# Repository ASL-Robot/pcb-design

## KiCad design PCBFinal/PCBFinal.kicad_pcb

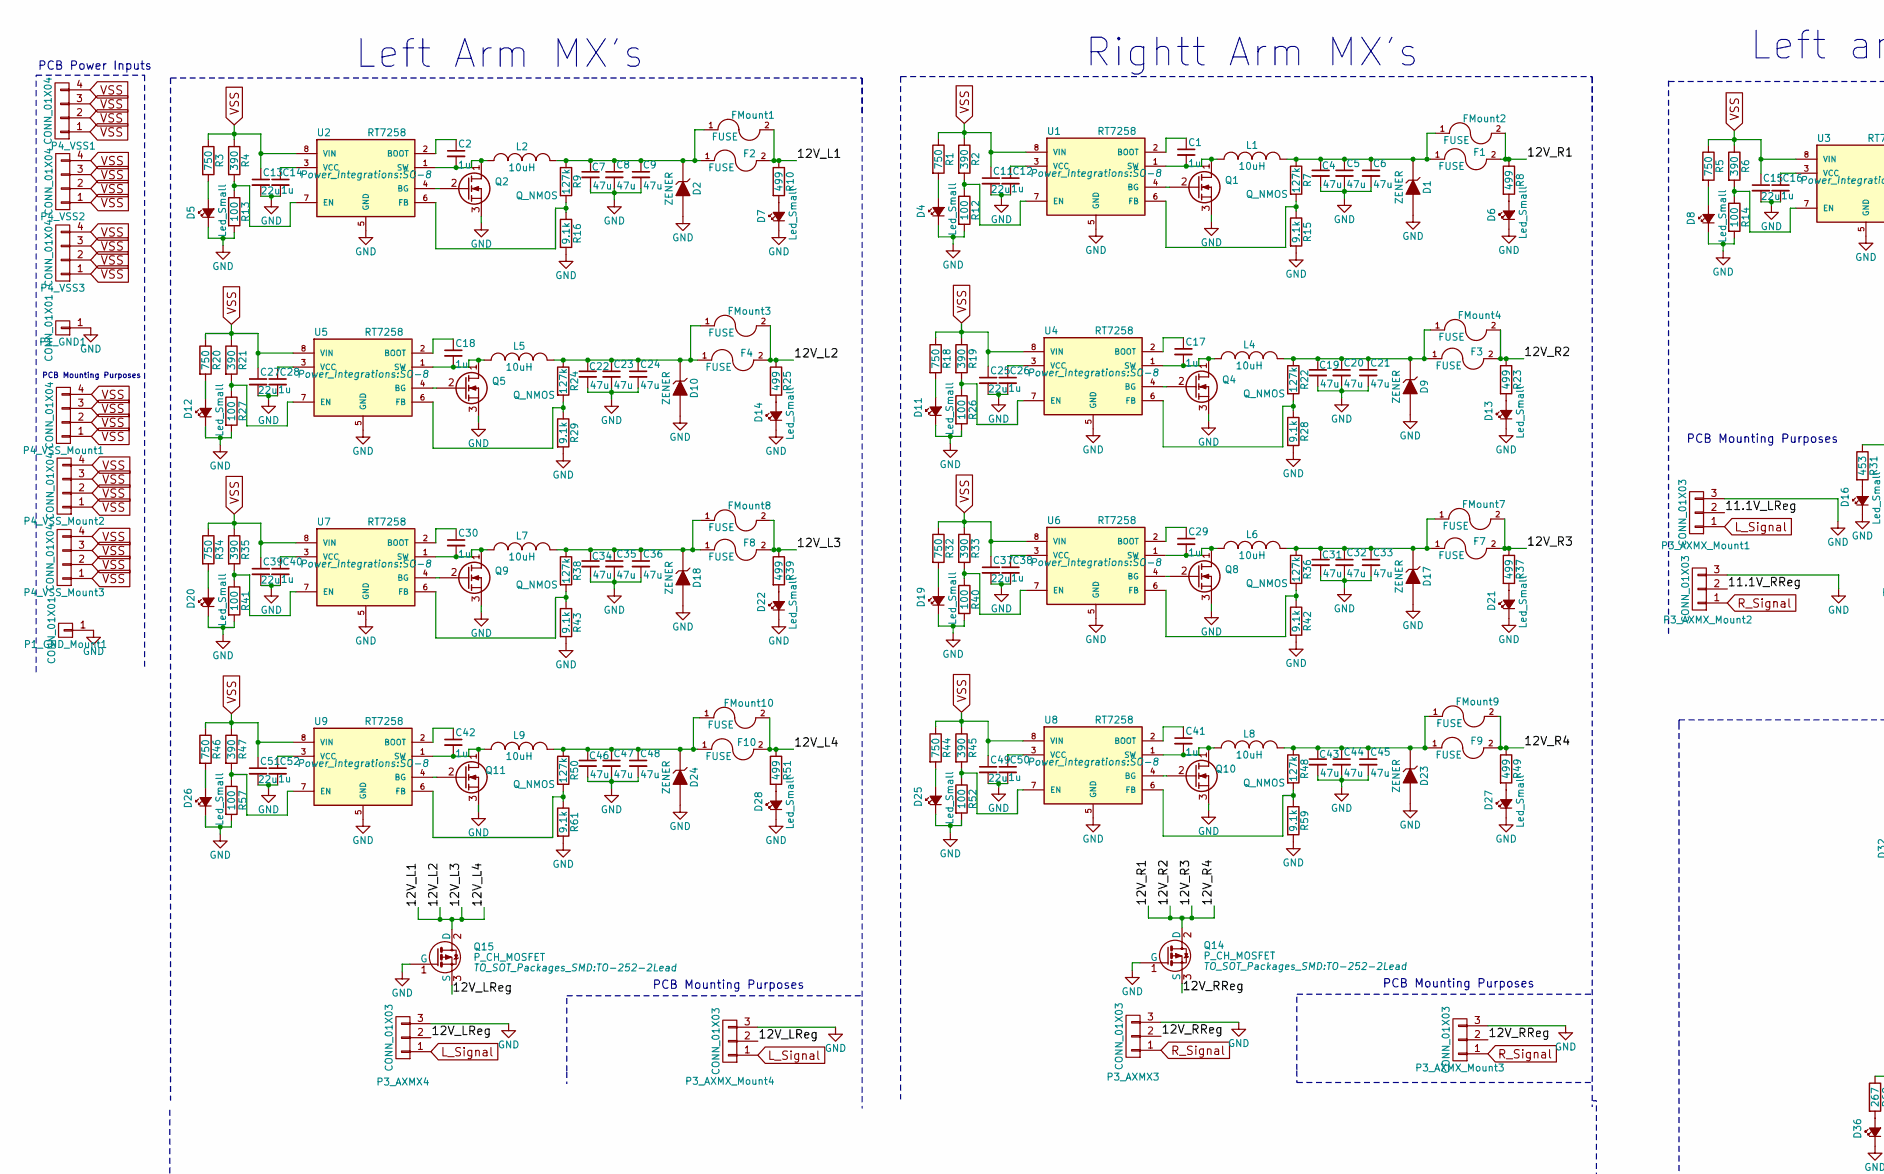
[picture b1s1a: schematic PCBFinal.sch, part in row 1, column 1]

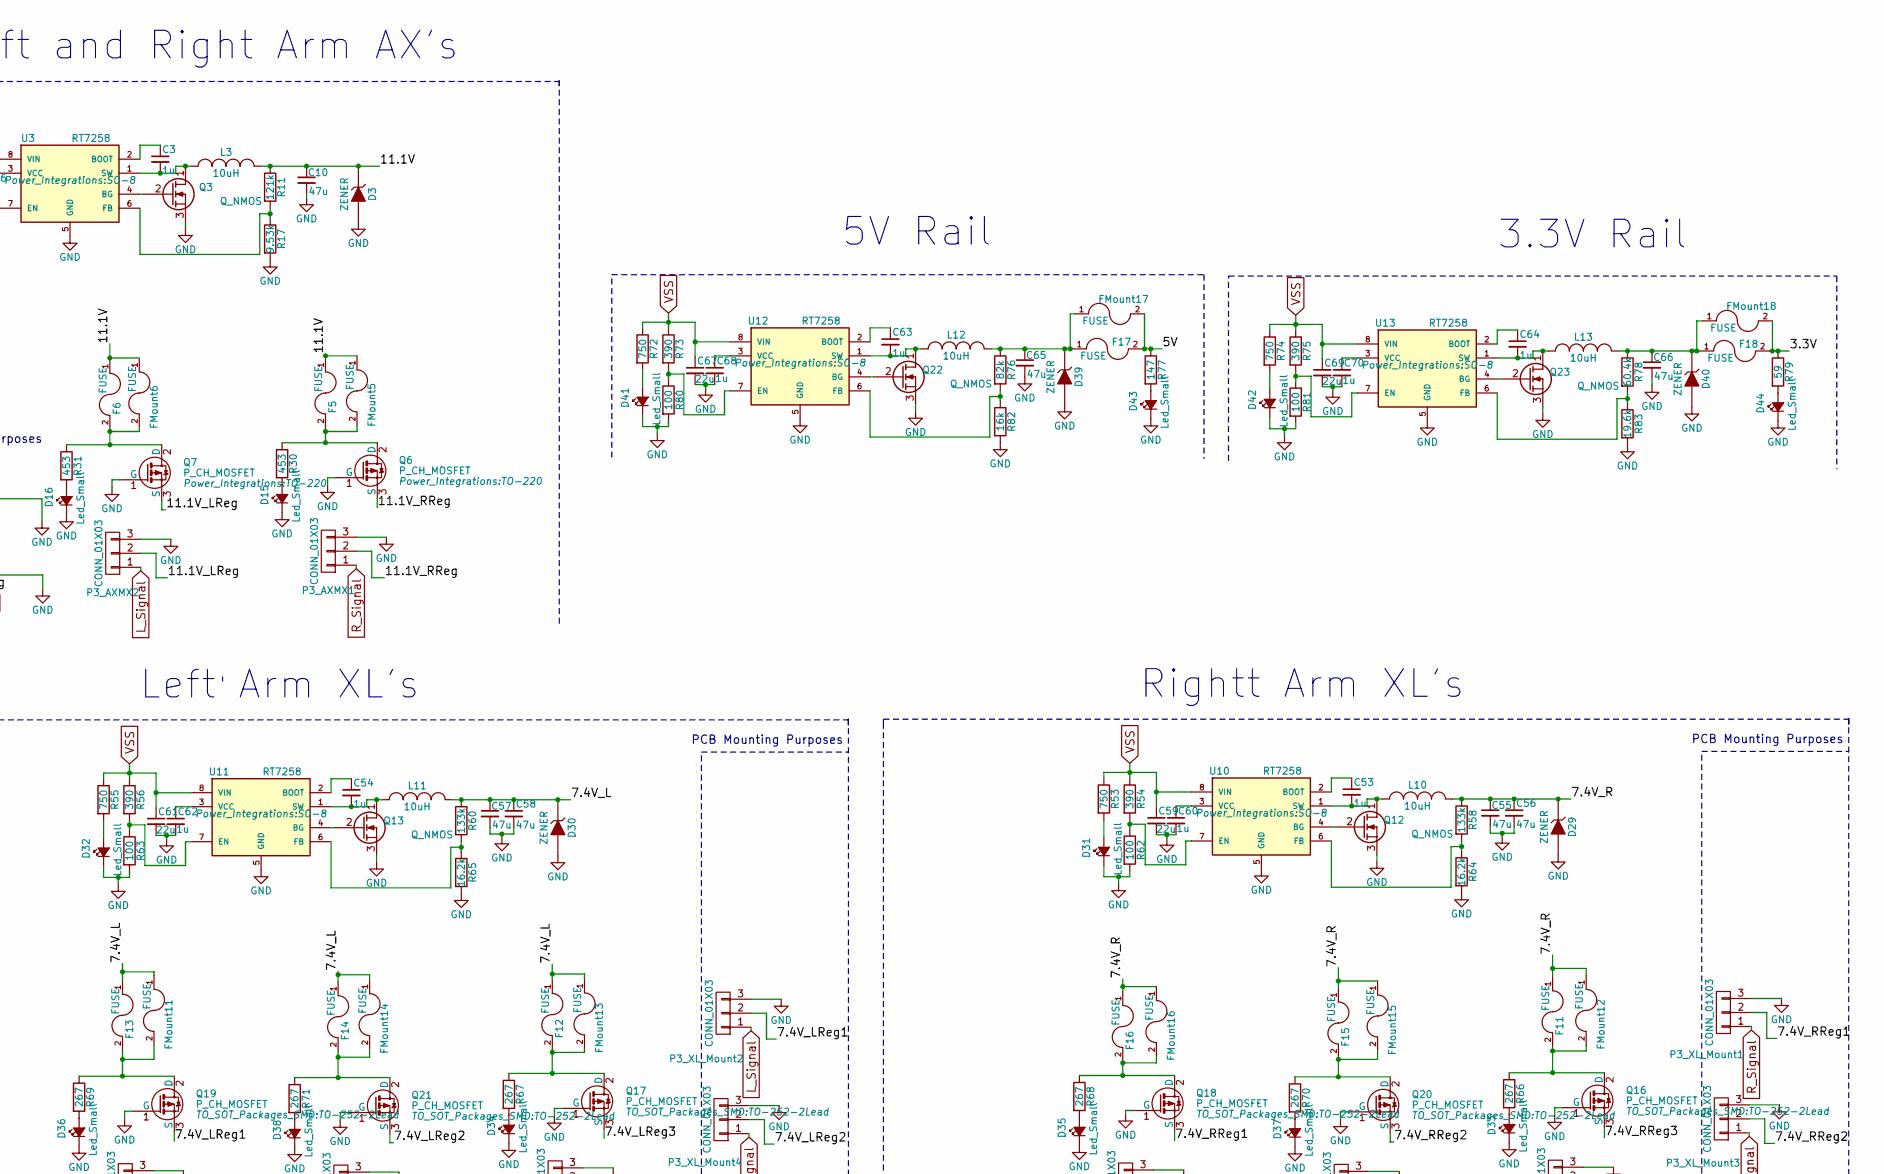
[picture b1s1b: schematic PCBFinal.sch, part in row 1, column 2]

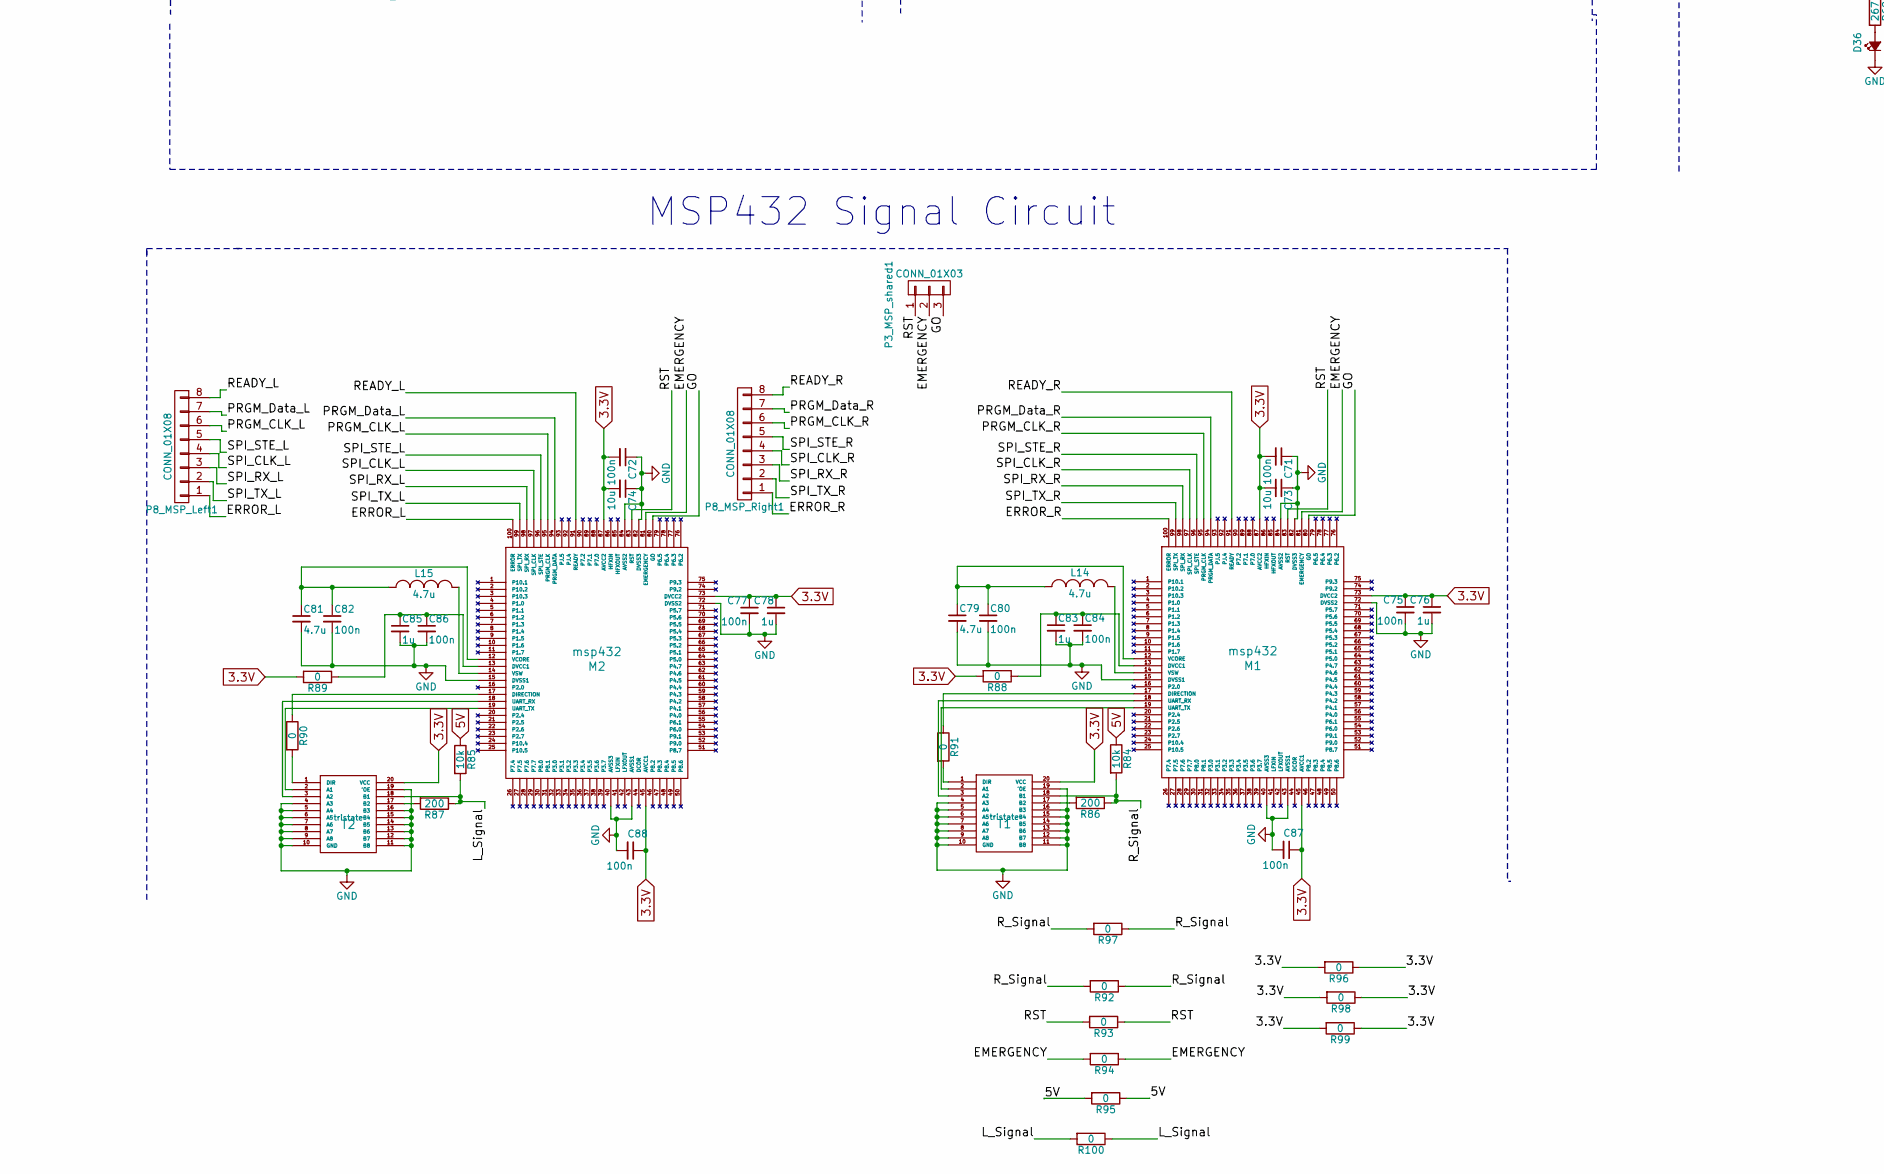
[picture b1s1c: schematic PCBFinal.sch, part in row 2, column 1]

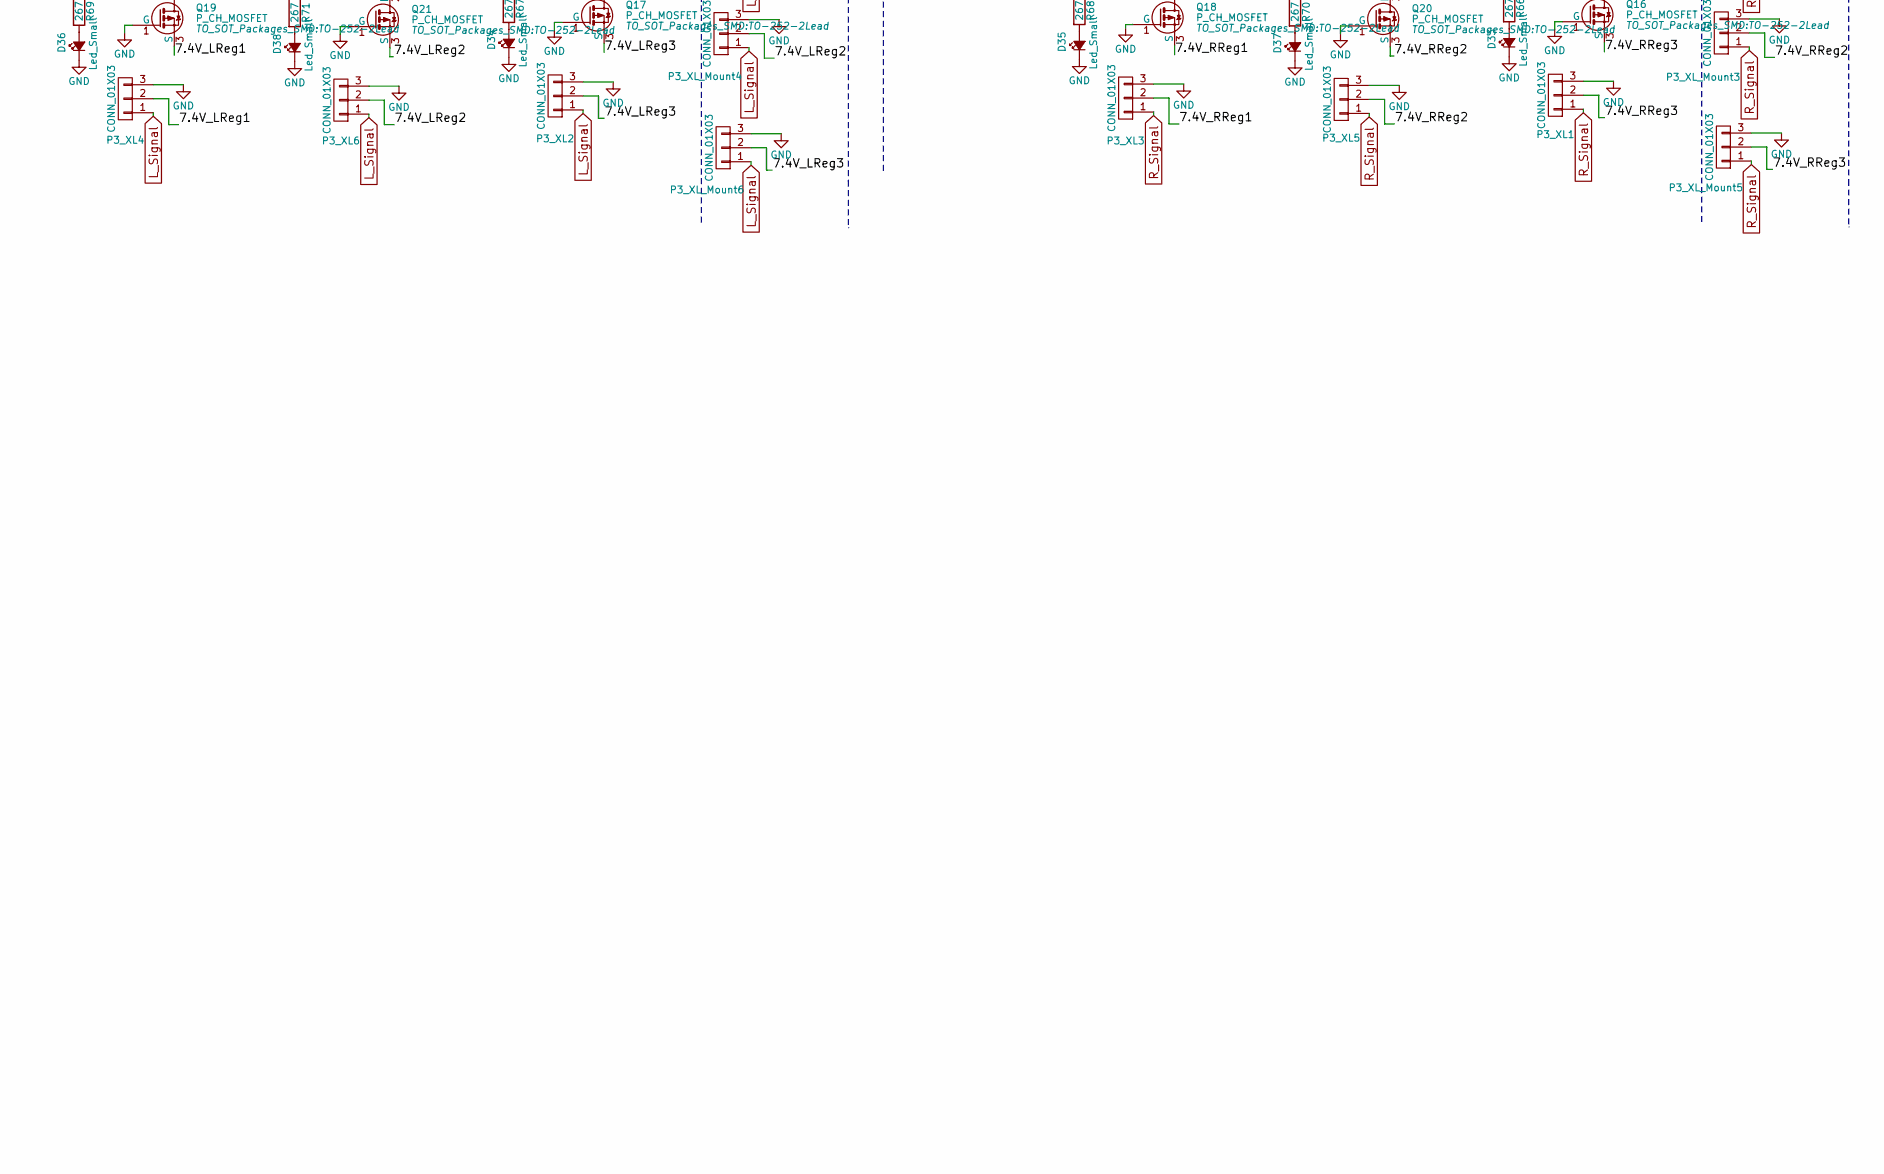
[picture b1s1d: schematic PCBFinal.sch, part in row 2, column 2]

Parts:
C1, C2, C3, C12, C14, C16, C17, C18, C26, C28, C29, C30, C38, C40, C41, C42, C50, C52, C53, C54, C60, C62, C63, C64, C68, C76, C78, C83, C85: 1u; C_1206_HandSoldering
C4, C5, C7, C8, C9, C10, C19, C20, C21, C22, C23, C24, C31, C32, C33, C34, C35, C36, C43, C44, C45, C46, C47, C48, C55, C56, C57, C58: 47u; C_1210_HandSoldering
C6: 47u; Q_NMOS
C11, C13, C15, C25, C27, C37, C39, C49, C51, C59, C61, C67: 22u; C_1206_HandSoldering
C65, C66: 47u; C_1206_HandSoldering
C69: 22u; C_1210_HandSoldering
C70: 1u; C_1210_HandSoldering
C71, C72, C75, C77, C80, C82, C84, C86, C87, C88: 100n; C_1206_HandSoldering
C73, C74: 10u; C_1206_HandSoldering
C79, C81: 4.7u; C_1206_HandSoldering
D1, D2, D3, D9, D10, D17, D18, D23, D24, D29, D30, D39, D40: ZENER; SMB_Handsoldering
D4, D5, D6, D7, D8, D11, D12, D13, D14, D15, D16, D19, D20, D21, D22, D25, D26, D27, D28, D31, D32, D33, D34, D35, D36, D37, D38, D41, D42, D43, D44: Led_Small; R_1206_HandSoldering
F1, F2, F3, F4, F5, F6, F7, F8, F9, F10, F11, F12, F13, F14, F15, F16, F17, F18: FUSE; Fuseholder5x20_horiz_open_Schurter_0031_8201
FMount1, FMount2, FMount3, FMount4, FMount5, FMount6, FMount7, FMount8, FMount9, FMount10, FMount11, FMount12, FMount13, FMount14, FMount15, FMount16, FMount17, FMount18: FUSE; FuseholderThroughHoles
L1, L2, L3, L4, L5, L6, L7, L8, L9, L10, L11, L12, L13: 10uH; 10uHInductor
L14, L15: 4.7u; C_1206_HandSoldering
M1, M2: msp432; LQFP-100_14x14mm_Pitch0.5mm
P1_GND1: CONN_01X01; GND_CONN
P1_GND_Mount1: CONN_01X01; GND_CONN_Holes
P3_AXMX1, P3_AXMX2, P3_AXMX3, P3_AXMX4: CONN_01X03; Pin_Header_Straight_1x03
P3_AXMX_Mount1, P3_AXMX_Mount2, P3_AXMX_Mount3, P3_AXMX_Mount4: CONN_01X03; Pin_Header_Straight_1x03_Holes
P3_MSP_shared1, P3_XL1, P3_XL2, P3_XL3, P3_XL4, P3_XL5, P3_XL6: CONN_01X03; Pin_Header_Straight_1x03_Pitch2.00mm
P3_XL_Mount1, P3_XL_Mount2, P3_XL_Mount3, P3_XL_Mount4, P3_XL_Mount5, P3_XL_Mount6: CONN_01X03; Pin_Header_Straight_1x03_Pitch2.00mm_Holes
P4_VSS1, P4_VSS2, P4_VSS3: CONN_01X04; TerminalBlock_Pheonix_PT-3.5mm_4pol
P4_VSS_Mount1, P4_VSS_Mount2, P4_VSS_Mount3: CONN_01X04; TerminalBlock_Pheonix_PT-3.5mm_4pol_Holes
P8_MSP_Left1, P8_MSP_Right1: CONN_01X08; Pin_Header_Straight_1x08_Pitch2.00mm_SMD
Q1, Q2, Q3, Q4, Q5, Q8, Q9, Q10, Q11, Q12, Q13, Q22, Q23: Q_NMOS
Q6, Q7: P_CH_MOSFET; TO-220
Q14, Q15, Q16, Q17, Q18, Q19, Q20, Q21: P_CH_MOSFET; TO-252-2Lead
R1, R3, R5, R18, R20, R32, R34, R44, R46, R53, R55, R72, R74: 750; R_1206_HandSoldering
R2, R4, R6, R19, R21, R33, R35, R45, R47, R54, R56, R73, R75: 390; R_1206_HandSoldering
R7, R9, R22, R24, R36, R38, R48, R50: 127k; R_1206_HandSoldering
R8, R10, R23, R25, R37, R39, R49, R51: 499; R_1206_HandSoldering
R11: 121k; R_1206_HandSoldering
R12, R13, R14, R26, R27, R40, R41, R52, R57, R62, R63, R80, R81: 100; R_1206_HandSoldering
R15, R16, R28, R29, R42, R43, R59, R61: 9.1k; R_1206_HandSoldering
R17: 9.53k; R_1206_HandSoldering
R30, R31: 453; R_1206_HandSoldering
R58, R60: 133k; R_1206_HandSoldering
R64, R65: 16.2k; R_1206_HandSoldering
R66, R67, R68, R69, R70, R71: 267; R_1206_HandSoldering
R76: 82k; R_1206_HandSoldering
R77: 147; R_1206_HandSoldering
R78: 60.4k; R_1206_HandSoldering
R79: 59; R_1206_HandSoldering
R82: 16k; R_1206_HandSoldering
R83: 19.6k; R_1206_HandSoldering
R84, R85: 10k; R_1206_HandSoldering
R86, R87: 200; R_1206_HandSoldering
R88, R89, R90, R91, R92, R93, R94, R95, R96, R97, R98, R99, R100: 0; R_1206_HandSoldering
T1, T2: tristate; SOIC-20_7.5x12.8mm_Pitch1.27mm
U1, U2, U3, U4, U5, U6, U7, U8, U9, U10, U11, U12, U13: RT7258; SO-8

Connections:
3.3V: C71.2, C72.2, C73.2, C74.2, C75.1, C76.1, C77.1, C78.1, C87.1, C88.1, F18.2, FMount18.2, M1.45 (AVCC1), M1.73 (DVCC2), M1.87 (AVCC2), M2.45 (AVCC1), M2.73 (DVCC2), M2.87 (AVCC2), R79.1, R88.2, R89.2, R96.1, R96.2, R98.1, R98.2, R99.1, R99.2, T1.20 (VCC), T2.20 (VCC)
5V: F17.2, FMount17.2, R77.1, R84.1, R85.1, R95.1, R95.2
/7.4V_L: C57.1, C58.1, D30.1 (K), F12.1, F13.1, F14.1, FMount11.1, FMount13.1, FMount14.1, L11.2, R60.1
/7.4V_LReg1: P3_XL4.2, P3_XL_Mount2.2, Q19.3 (S)
/7.4V_LReg2: P3_XL6.2, P3_XL_Mount4.2, Q21.3 (S)
/7.4V_LReg3: P3_XL2.2, P3_XL_Mount6.2, Q17.3 (S)
/7.4V_R: C55.1, C56.1, D29.1 (K), F11.1, F15.1, F16.1, FMount12.1, FMount15.1, FMount16.1, L10.2, R58.1
/7.4V_RReg1: P3_XL3.2, P3_XL_Mount1.2, Q18.3 (S)
/7.4V_RReg2: P3_XL5.2, P3_XL_Mount3.2, Q20.3 (S)
/7.4V_RReg3: P3_XL1.2, P3_XL_Mount5.2, Q16.3 (S)
/11.1V: C10.1, D3.1 (K), F5.1, F6.1, FMount5.1, FMount6.1, L3.2, R11.1
/11.1V_LReg: P3_AXMX2.2, P3_AXMX_Mount1.2, Q7.3 (S)
/11.1V_RReg: P3_AXMX1.2, P3_AXMX_Mount2.2, Q6.3 (S)
/12V_L1: F2.2, F4.2, F8.2, F10.2, FMount1.2, FMount3.2, FMount8.2, FMount10.2, Q15.2 (D), R10.1, R25.1, R39.1, R51.1
/12V_LReg: P3_AXMX4.2, P3_AXMX_Mount4.2, Q15.3 (S)
/12V_R1: F1.2, F3.2, F7.2, F9.2, FMount2.2, FMount4.2, FMount7.2, FMount9.2, Q14.2 (D), R8.1, R23.1, R37.1, R49.1
/12V_RReg: P3_AXMX3.2, P3_AXMX_Mount3.2, Q14.3 (S)
/EMERGENCY: M1.81 (EMERGENCY), M2.81 (EMERGENCY), P3_MSP_shared1.2, R94.1, R94.2
/ERROR_L: M2.100 (ERROR), P8_MSP_Left1.1
/ERROR_R: M1.100 (ERROR), P8_MSP_Right1.1
/GO: M1.80 (GO), M2.80 (GO), P3_MSP_shared1.3
/PRGM_CLK_L: M2.95 (PRGM_CLK), P8_MSP_Left1.6
/PRGM_CLK_R: M1.95 (PRGM_CLK), P8_MSP_Right1.6
/PRGM_Data_L: M2.94 (PRGM_DATA), P8_MSP_Left1.7
/PRGM_Data_R: M1.94 (PRGM_DATA), P8_MSP_Right1.7
/READY_L: M2.91 (READY), P8_MSP_Left1.8
/READY_R: M1.91 (READY), P8_MSP_Right1.8
/RST: M1.83 (RST), M2.83 (RST), P3_MSP_shared1.1, R93.1, R93.2
/SPI_CLK_L: M2.97 (SPI_CLK), P8_MSP_Left1.4
/SPI_CLK_R: M1.97 (SPI_CLK), P8_MSP_Right1.4
/SPI_RX_L: M2.98 (SPI_RX), P8_MSP_Left1.3
/SPI_RX_R: M1.98 (SPI_RX), P8_MSP_Right1.3
/SPI_STE_L: M2.96 (SPI_STE), P8_MSP_Left1.5
/SPI_STE_R: M1.96 (SPI_STE), P8_MSP_Right1.5
/SPI_TX_L: M2.99 (SPI_TX), P8_MSP_Left1.2
/SPI_TX_R: M1.99 (SPI_TX), P8_MSP_Right1.2
GND: C4.2, C5.2, C6.2, C7.2, C8.2, C9.2, C10.2, C11.2, C12.2, C13.2, C14.2, C15.2, C16.2, C19.2, C20.2, C21.2, C22.2, C23.2, C24.2, C25.2, C26.2, C27.2, C28.2, C31.2, C32.2, C33.2, C34.2, C35.2, C36.2, C37.2, C38.2, C39.2, C40.2, C43.2, C44.2, C45.2, C46.2, C47.2, C48.2, C49.2, C50.2, C51.2, C52.2, C55.2, C56.2, C57.2, C58.2, C59.2, C60.2, C61.2, C62.2, C65.2, C66.2, C67.2, C68.2, C69.2, C70.2, C71.1, C72.1, C73.1, C74.1, C75.2, C76.2, C77.2, C78.2, C79.2, C80.2, C81.2, C82.2, C83.2, C84.2, C85.2, C86.2, C87.2, C88.2, D1.2 (A), D2.2 (A), D3.2 (A), D4.1 (K), D5.1 (K), D6.1 (K), D7.1 (K), D8.1 (K), D9.2 (A), D10.2 (A), D11.1 (K), D12.1 (K), D13.1 (K), D14.1 (K), D15.1 (K), D16.1 (K), D17.2 (A), D18.2 (A), D19.1 (K), D20.1 (K), D21.1 (K), D22.1 (K), D23.2 (A), D24.2 (A), D25.1 (K), D26.1 (K), D27.1 (K), D28.1 (K), D29.2 (A), D30.2 (A), D31.1 (K), D32.1 (K), D33.1 (K), D34.1 (K), D35.1 (K), D36.1 (K), D37.1 (K), D38.1 (K), D39.2 (A), D40.2 (A), D41.1 (K), D42.1 (K), D43.1 (K), D44.1 (K), M1.15 (DVSS1), M1.40 (AVSS3), M1.43 (AVSS1), M1.72 (DVSS2), M1.82 (DVSS3), M1.84 (AVSS2), M2.15 (DVSS1), M2.40 (AVSS3), M2.43 (AVSS1), M2.72 (DVSS2), M2.82 (DVSS3), M2.84 (AVSS2), P1_GND1.1, P1_GND_Mount1.1, P3_AXMX1.3, P3_AXMX2.3, P3_AXMX3.3, P3_AXMX4.3, P3_AXMX_Mount1.3, P3_AXMX_Mount2.3, P3_AXMX_Mount3.3, P3_AXMX_Mount4.3, P3_XL1.3, P3_XL2.3, P3_XL3.3, P3_XL4.3, P3_XL5.3, P3_XL6.3, P3_XL_Mount1.3, P3_XL_Mount2.3, P3_XL_Mount3.3, P3_XL_Mount4.3, P3_XL_Mount5.3, P3_XL_Mount6.3, Q1.3 (S), Q2.3 (S), Q3.3 (S), Q4.3 (S), Q5.3 (S), Q6.1 (G), Q7.1 (G), Q8.3 (S), Q9.3 (S), Q10.3 (S), Q11.3 (S), Q12.3 (S), Q13.3 (S), Q14.1 (G), Q15.1 (G), Q16.1 (G), Q17.1 (G), Q18.1 (G), Q19.1 (G), Q20.1 (G), Q21.1 (G), Q22.3 (S), Q23.3 (S), R12.2, R13.2, R14.2, R15.2, R16.2, R17.2, R26.2, R27.2, R28.2, R29.2, R40.2, R41.2, R42.2, R43.2, R52.2, R57.2, R59.2, R61.2, R62.2, R63.2, R64.2, R65.2, R80.2, R81.2, R82.2, R83.2, T1.4 (A3), T1.5 (A4), T1.6 (A5), T1.7 (A6), T1.8 (A7), T1.9 (A8), T1.10 (GND), T1.11 (B8), T1.12 (B7), T1.13 (B6), T1.14 (B5), T1.15 (B4), T1.16 (B3), T1.19 ('OE), T2.4 (A3), T2.5 (A4), T2.6 (A5), T2.7 (A6), T2.8 (A7), T2.9 (A8), T2.10 (GND), T2.11 (B8), T2.12 (B7), T2.13 (B6), T2.14 (B5), T2.15 (B4), T2.16 (B3), T2.19 ('OE), U1.5 (GND), U2.5 (GND), U3.5 (GND), U4.5 (GND), U5.5 (GND), U6.5 (GND), U7.5 (GND), U8.5 (GND), U9.5 (GND), U10.5 (GND), U11.5 (GND), U12.5 (GND), U13.5 (GND)
L_Signal: P3_AXMX2.1, P3_AXMX4.1, P3_AXMX_Mount1.1, P3_AXMX_Mount4.1, P3_XL2.1, P3_XL4.1, P3_XL6.1, P3_XL_Mount2.1, P3_XL_Mount4.1, P3_XL_Mount6.1, R85.2, R87.1, R100.1, R100.2, T2.18 (B1)
unnamed: C1.1, U1.2 (BOOT)
unnamed: C1.2, L1.1, Q1.1 (D), U1.1 (SW)
unnamed: C2.1, U2.2 (BOOT)
unnamed: C2.2, L2.1, Q2.1 (D), U2.1 (SW)
unnamed: C3.1, U3.2 (BOOT)
unnamed: C3.2, L3.1, Q3.1 (D), U3.1 (SW)
unnamed: C4.1, C5.1, C6.1, D1.1 (K), F1.1, FMount2.1, L1.2, R7.1
unnamed: C7.1, C8.1, C9.1, D2.1 (K), F2.1, FMount1.1, L2.2, R9.1
unnamed: C12.1, U1.3 (VCC)
unnamed: C14.1, U2.3 (VCC)
unnamed: C16.1, U3.3 (VCC)
unnamed: C17.1, U4.2 (BOOT)
unnamed: C17.2, L4.1, Q4.1 (D), U4.1 (SW)
unnamed: C18.1, U5.2 (BOOT)
unnamed: C18.2, L5.1, Q5.1 (D), U5.1 (SW)
unnamed: C19.1, C20.1, C21.1, D9.1 (K), F3.1, FMount4.1, L4.2, R22.1
unnamed: C22.1, C23.1, C24.1, D10.1 (K), F4.1, FMount3.1, L5.2, R24.1
unnamed: C26.1, U4.3 (VCC)
unnamed: C28.1, U5.3 (VCC)
unnamed: C29.1, U6.2 (BOOT)
unnamed: C29.2, L6.1, Q8.1 (D), U6.1 (SW)
unnamed: C30.1, U7.2 (BOOT)
unnamed: C30.2, L7.1, Q9.1 (D), U7.1 (SW)
unnamed: C31.1, C32.1, C33.1, D17.1 (K), F7.1, FMount7.1, L6.2, R36.1
unnamed: C34.1, C35.1, C36.1, D18.1 (K), F8.1, FMount8.1, L7.2, R38.1
unnamed: C38.1, U6.3 (VCC)
unnamed: C40.1, U7.3 (VCC)
unnamed: C41.1, U8.2 (BOOT)
unnamed: C41.2, L8.1, Q10.1 (D), U8.1 (SW)
unnamed: C42.1, U9.2 (BOOT)
unnamed: C42.2, L9.1, Q11.1 (D), U9.1 (SW)
unnamed: C43.1, C44.1, C45.1, D23.1 (K), F9.1, FMount9.1, L8.2, R48.1
unnamed: C46.1, C47.1, C48.1, D24.1 (K), F10.1, FMount10.1, L9.2, R50.1
unnamed: C50.1, U8.3 (VCC)
unnamed: C52.1, U9.3 (VCC)
unnamed: C53.1, U10.2 (BOOT)
unnamed: C53.2, L10.1, Q12.1 (D), U10.1 (SW)
unnamed: C54.1, U11.2 (BOOT)
unnamed: C54.2, L11.1, Q13.1 (D), U11.1 (SW)
unnamed: C60.1, U10.3 (VCC)
unnamed: C62.1, U11.3 (VCC)
unnamed: C63.1, U12.2 (BOOT)
unnamed: C63.2, L12.1, Q22.1 (D), U12.1 (SW)
unnamed: C64.1, U13.2 (BOOT)
unnamed: C64.2, L13.1, Q23.1 (D), U13.1 (SW)
unnamed: C65.1, D39.1 (K), F17.1, FMount17.1, L12.2, R76.1
unnamed: C66.1, D40.1 (K), F18.1, FMount18.1, L13.2, R78.1
unnamed: C68.1, U12.3 (VCC)
unnamed: C70.1, U13.3 (VCC)
unnamed: C79.1, C80.1, L14.1, M1.12 (VCORE)
unnamed: C81.1, C82.1, L15.1, M2.12 (VCORE)
unnamed: C83.1, C84.1, M1.13 (DVCC1), R88.1
unnamed: C85.1, C86.1, M2.13 (DVCC1), R89.1
unnamed: D4.2 (A), R1.2
unnamed: D5.2 (A), R3.2
unnamed: D6.2 (A), R8.2
unnamed: D7.2 (A), R10.2
unnamed: D8.2 (A), R5.2
unnamed: D11.2 (A), R18.2
unnamed: D12.2 (A), R20.2
unnamed: D13.2 (A), R23.2
unnamed: D14.2 (A), R25.2
unnamed: D15.2 (A), R30.2
unnamed: D16.2 (A), R31.2
unnamed: D19.2 (A), R32.2
unnamed: D20.2 (A), R34.2
unnamed: D21.2 (A), R37.2
unnamed: D22.2 (A), R39.2
unnamed: D25.2 (A), R44.2
unnamed: D26.2 (A), R46.2
unnamed: D27.2 (A), R49.2
unnamed: D28.2 (A), R51.2
unnamed: D31.2 (A), R53.2
unnamed: D32.2 (A), R55.2
unnamed: D33.2 (A), R66.2
unnamed: D34.2 (A), R67.2
unnamed: D35.2 (A), R68.2
unnamed: D36.2 (A), R69.2
unnamed: D37.2 (A), R70.2
unnamed: D38.2 (A), R71.2
unnamed: D41.2 (A), R72.2
unnamed: D42.2 (A), R74.2
unnamed: D43.2 (A), R77.2
unnamed: D44.2 (A), R79.2
unnamed: F5.2, FMount5.2, Q6.2 (D), R30.1
unnamed: F6.2, FMount6.2, Q7.2 (D), R31.1
unnamed: F11.2, FMount12.2, Q16.2 (D), R66.1
unnamed: F12.2, FMount13.2, Q17.2 (D), R67.1
unnamed: F13.2, FMount11.2, Q19.2 (D), R69.1
unnamed: F14.2, FMount14.2, Q21.2 (D), R71.1
unnamed: F15.2, FMount15.2, Q20.2 (D), R70.1
unnamed: F16.2, FMount16.2, Q18.2 (D), R68.1
unnamed: L14.2, M1.14 (VSW)
unnamed: L15.2, M2.14 (VSW)
unnamed: M1.17 (DIRECTION), R91.1
unnamed: M1.18 (UART_RX), T1.3 (A2)
unnamed: M1.19 (UART_TX), T1.2 (A1)
unnamed: M2.17 (DIRECTION), R90.1
unnamed: M2.18 (UART_RX), T2.3 (A2)
unnamed: M2.19 (UART_TX), T2.2 (A1)
unnamed: Q1.2 (G), U1.4 (BG)
unnamed: Q2.2 (G), U2.4 (BG)
unnamed: Q3.2 (G), U3.4 (BG)
unnamed: Q4.2 (G), U4.4 (BG)
unnamed: Q5.2 (G), U5.4 (BG)
unnamed: Q8.2 (G), U6.4 (BG)
unnamed: Q9.2 (G), U7.4 (BG)
unnamed: Q10.2 (G), U8.4 (BG)
unnamed: Q11.2 (G), U9.4 (BG)
unnamed: Q12.2 (G), U10.4 (BG)
unnamed: Q13.2 (G), U11.4 (BG)
unnamed: Q22.2 (G), U12.4 (BG)
unnamed: Q23.2 (G), U13.4 (BG)
unnamed: R11.2, R17.1, U3.6 (FB)
unnamed: R2.2, R12.1, U1.7 (EN)
unnamed: R4.2, R13.1, U2.7 (EN)
unnamed: R6.2, R14.1, U3.7 (EN)
unnamed: R7.2, R15.1, U1.6 (FB)
unnamed: R9.2, R16.1, U2.6 (FB)
unnamed: R19.2, R26.1, U4.7 (EN)
unnamed: R21.2, R27.1, U5.7 (EN)
unnamed: R22.2, R28.1, U4.6 (FB)
unnamed: R24.2, R29.1, U5.6 (FB)
unnamed: R33.2, R40.1, U6.7 (EN)
unnamed: R35.2, R41.1, U7.7 (EN)
unnamed: R36.2, R42.1, U6.6 (FB)
unnamed: R38.2, R43.1, U7.6 (FB)
unnamed: R45.2, R52.1, U8.7 (EN)
unnamed: R47.2, R57.1, U9.7 (EN)
unnamed: R48.2, R59.1, U8.6 (FB)
unnamed: R50.2, R61.1, U9.6 (FB)
unnamed: R54.2, R62.1, U10.7 (EN)
unnamed: R56.2, R63.1, U11.7 (EN)
unnamed: R58.2, R64.1, U10.6 (FB)
unnamed: R60.2, R65.1, U11.6 (FB)
unnamed: R73.2, R80.1, U12.7 (EN)
unnamed: R75.2, R81.1, U13.7 (EN)
unnamed: R76.2, R82.1, U12.6 (FB)
unnamed: R78.2, R83.1, U13.6 (FB)
unnamed: R86.2, T1.17 (B2)
unnamed: R87.2, T2.17 (B2)
unnamed: R90.2, T2.1 (DIR)
unnamed: R91.2, T1.1 (DIR)
R_Signal: P3_AXMX1.1, P3_AXMX3.1, P3_AXMX_Mount2.1, P3_AXMX_Mount3.1, P3_XL1.1, P3_XL3.1, P3_XL5.1, P3_XL_Mount1.1, P3_XL_Mount3.1, P3_XL_Mount5.1, R84.2, R86.1, R92.1, R92.2, R97.1, R97.2, T1.18 (B1)
VSS: C11.1, C13.1, C15.1, C25.1, C27.1, C37.1, C39.1, C49.1, C51.1, C59.1, C61.1, C67.1, C69.1, P4_VSS1.1, P4_VSS1.2, P4_VSS1.3, P4_VSS1.4, P4_VSS2.1, P4_VSS2.2, P4_VSS2.3, P4_VSS2.4, P4_VSS3.1, P4_VSS3.2, P4_VSS3.3, P4_VSS3.4, P4_VSS_Mount1.1, P4_VSS_Mount1.2, P4_VSS_Mount1.3, P4_VSS_Mount1.4, P4_VSS_Mount2.1, P4_VSS_Mount2.2, P4_VSS_Mount2.3, P4_VSS_Mount2.4, P4_VSS_Mount3.1, P4_VSS_Mount3.2, P4_VSS_Mount3.3, P4_VSS_Mount3.4, R1.1, R2.1, R3.1, R4.1, R5.1, R6.1, R18.1, R19.1, R20.1, R21.1, R32.1, R33.1, R34.1, R35.1, R44.1, R45.1, R46.1, R47.1, R53.1, R54.1, R55.1, R56.1, R72.1, R73.1, R74.1, R75.1, U1.8 (VIN), U2.8 (VIN), U3.8 (VIN), U4.8 (VIN), U5.8 (VIN), U6.8 (VIN), U7.8 (VIN), U8.8 (VIN), U9.8 (VIN), U10.8 (VIN), U11.8 (VIN), U12.8 (VIN), U13.8 (VIN)

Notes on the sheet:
Left Arm MX's
Left and Right Arm AX's
Left Arm XL's
5V Rail
3.3V Rail
MSP432 Signal Circuit
PCB Mounting Purposes
Rightt Arm MX's
PCB Mounting Purposes
Rightt Arm XL's
PCB Power Inputs

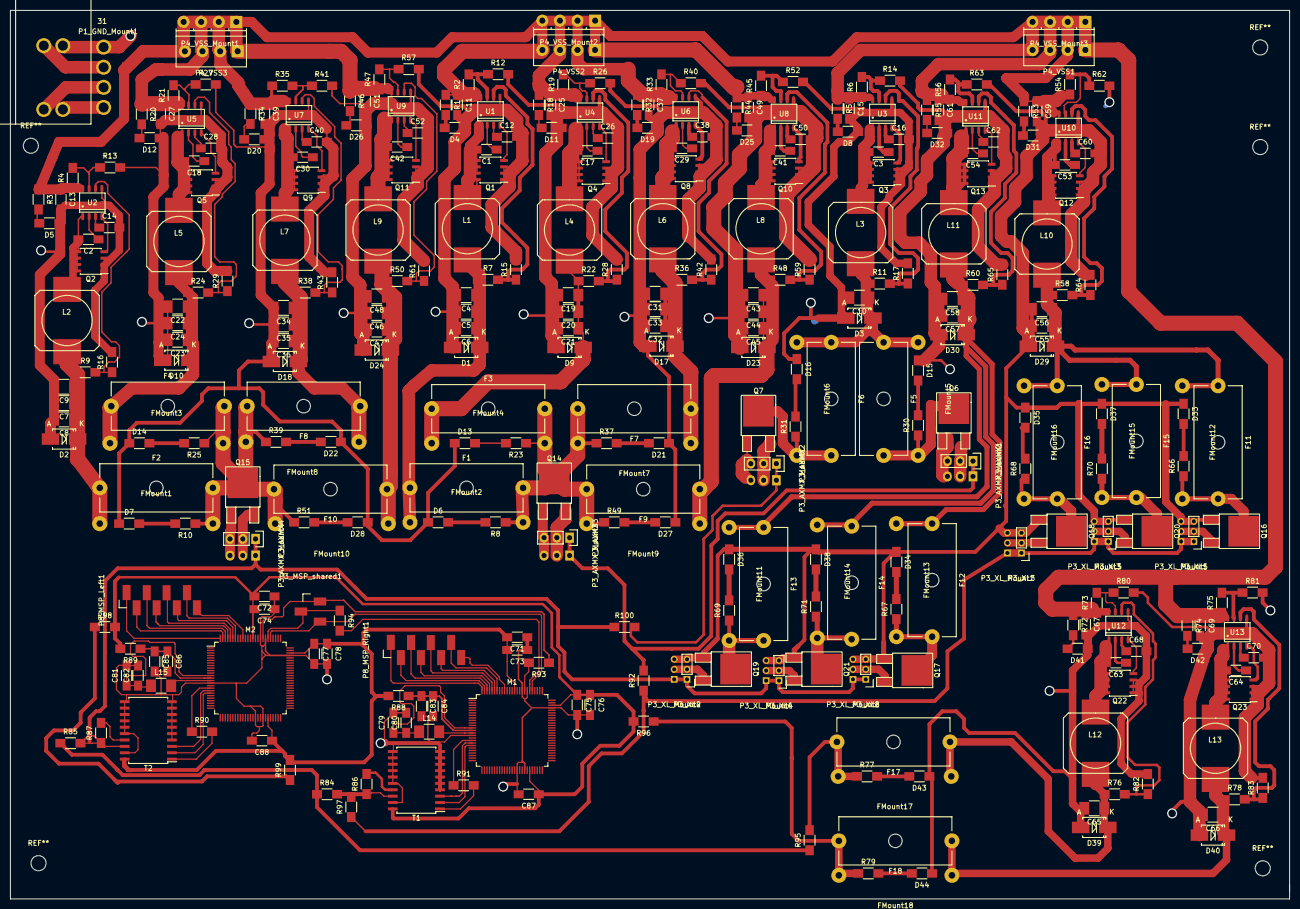
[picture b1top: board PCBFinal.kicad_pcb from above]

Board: 2 copper layers, 254.5 x 176.8 mm, 354 parts (0 on the bottom side), 183 nets.

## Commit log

2016-05-11 Adding Circuit BOM and PCB files
